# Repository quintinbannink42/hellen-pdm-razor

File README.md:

# PowerCore

Hellen-One **hardware** for **PowerCore**, a standalone automotive power distribution module (PDM) with a **Link Razor PDM**-compatible SuperSeal loom.

| | |
|---|---|
| **Product** | **PowerCore** (not an engine ECU) |
| **Connector** | 26-pin AMP SuperSeal 1.0 (Link “Connector C”) — pinout in [CONNECTOR.md](CONNECTOR.md) |
| **Main power** | M6 + / − (VBAT / GND), not on the SuperSeal |
| **MCU module** | [mega-mcu144](https://github.com/andreika-git/hellen-one/tree/master/modules/mega-mcu144) **rev ≥ 0.7** (STM32F767) |
| **I/O target** | 4× high-power (25 A / 80 A peak class) + 8× ADIO (8 A) |
| **KiCad stem** | `pdmrazora` (hellen-one: no dashes/underscores — **do not rename**) |
| **GitHub path** | `hellen-pdm-razor` (legacy repo name; product name is PowerCore) |
| **Default branch** | `main` (required by hellen-one automation) |

> **This is NOT [HELLCORE](https://github.com/quintinbannink42/HELLCORE).** HELLCORE is a separate project. PowerCore is a Hellen-One PDM carrier that matches the Link Razor loom connector.

Former working names (docs/history only): `hellen-pdm-razor`, Hellen Razor-class PDM.

## Docs

| File | Contents |
|------|----------|
| [POWERCORE_BRIEF.md](POWERCORE_BRIEF.md) | Product identity, tokens, Razor loom compatibility |
| [CONNECTOR.md](CONNECTOR.md) | Exact Razor-compatible 26-pin + M6 pinout (authoritative) |
| [PINMAP.md](PINMAP.md) | mega-mcu144 edge → HP / ADIO / system nets |
| [REV1_SPEC.md](REV1_SPEC.md) | Goals, architecture, e-fuse behaviour |
| [BLOCK_DIAGRAM.md](BLOCK_DIAGRAM.md) | Carrier block diagram |
| [BOARD.md](BOARD.md) | What’s stubbed vs next; module placement steps |
| [HARDWARE_BOM.md](HARDWARE_BOM.md) | Chosen PNs, kILIS, AmpsPerVolt TODOs |

## KiCad project

Open with **KiCad 8.x** (Hellen mega-mcu144 0.7 is K8). KiCad 9 also works. KiCad 6/7 will not open this module.

- `pdmrazora.kicad_pro` / `.kicad_sch` / `.kicad_pcb` (no dashes/underscores — hellen-one requirement)
- `revision.txt` → `BOARD_PREFIX=pdm` `BOARD_SUFFIX=razor` `BOARD_REVISION=a`

Schematic: SuperSeal **TE 6473418-1** vertical (Link Razor-compatible nets; same pin numbers as former RA 9-6437287-8), **split** M6 bolt-through bobbins (J2 VBAT+ north / J3 GND south, drivers between) + power entry/IGN_SW divider, sheets **MM144** / **HP** (**BTS50010-1TAD** ×4) / **ADIO** (**BTS7004-1EPP** ×8 + sense/PU). PCB: **109×98 mm** frame (was 104×93), mega-mcu144 0.7 west of a vertical SuperSeal EMI wall, power/PROFET east. J2 VBAT+ and J3 GND stay on opposite edges of the power field; HP×4 and ADIO×8 are mirrored about x=80. `PWR_OUT1–4` run on exposed F.Cu (F.Mask opened over the copper) with short B.Cu hops only at the module pad wall. DRC shorts/crossings/clearance are 0; the board is not fab-clean (see [BOARD.md](BOARD.md)). Parts/kILIS: [HARDWARE_BOM.md](HARDWARE_BOM.md).

## How to build (Hellen-One)

1. `git clone --recurse-submodules https://github.com/quintinbannink42/hellen-pdm-razor.git`
2. Open with **KiCad 8.x** (Hellen mega-mcu144 0.7 is K8). KiCad 9 also works. KiCad 6/7 will not open this module.
   Open `pdmrazora.kicad_pro`.
3. mega-mcu144 **0.7** is already on the frame (`M1000`). Refresh from `hellen-one/modules/mega-mcu144/0.7/` if the submodule moves.
4. Route SuperSeal / M6 / module pads per CONNECTOR.md / PINMAP.md; replace HP/ADIO schematic stubs with chosen PNs + sense parts.
5. Push to **`main`**. GitHub Action `.github/workflows/create-board.yaml` calls hellen-one create-board to merge module gerbers into `boards/`.
6. Daily workflows keep `hellen-one` and `kicad6-libraries` submodule refs updated.

Frame rules (from hellen-example FAQ):

- No `-` or `_` in KiCad filenames
- `aux_axis_origin` required; board origin at **bottom-left** (no negative coordinates)

## Firmware intent

Firmware is **not** this repo. See **[fw-powercore](https://github.com/quintinbannink42/fw-powercore)** (rusEFI custom board overlay: electronic fuse + channel map), based on [fw-custom-hellen144-f4](https://github.com/rusefi/fw-custom-hellen144-f4) / `hellen-common-mega144.mk`, with `protected_gpio` for HP1–4 + ADIO1–4 first. See PINMAP.md and REV1_SPEC.md.

## Submodules

```
hellen-one          https://github.com/andreika-git/hellen-one
kicad6-libraries    https://github.com/rusefi/kicad6-libraries
```

Skeleton mirrors [rusefi/hellen-example](https://github.com/rusefi/hellen-example).

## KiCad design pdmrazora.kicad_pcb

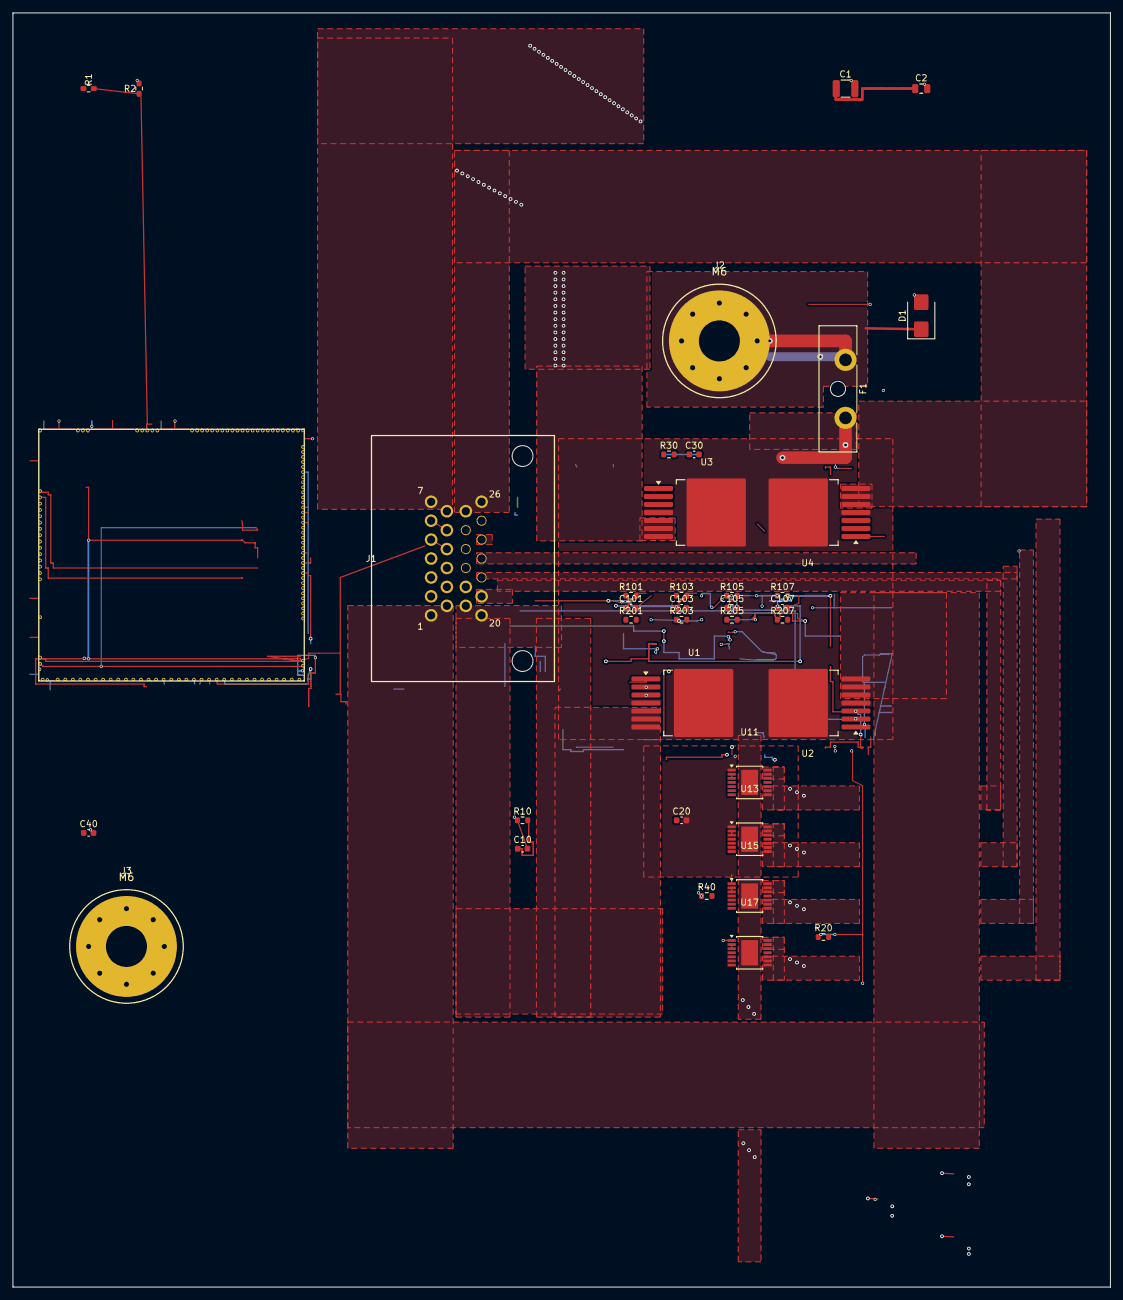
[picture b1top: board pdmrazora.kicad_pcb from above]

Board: 2 copper layers, 174.0 x 202.0 mm, 38 parts (0 on the bottom side), 32 nets.

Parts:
C1: 100u_50V; C_1210_3225Metric
C2: 100n; C_0805_2012Metric
C10, C20, C30, C40, C101, C103, C105, C107: 10n; C_0603_1608Metric
D1: SMBJ33CA; D_SMB
F1: 150A_MEGA_TBD; Fuseholder_Blade_ATO_Littelfuse_Pudenz_2_Pin
J1: 6473418-1; TE_6473418-1_SuperSeal26_Vertical
J2: M6_VBAT; M6_BoltThrough_Bobbin
J3: M6_GND; M6_BoltThrough_Bobbin
M1000: Module:mega-mcu144/0.7; mega-mcu144
R1: 100k; R_0603_1608Metric
R2: 10k; R_0603_1608Metric
R10, R20, R30, R40: 2k7; R_0603_1608Metric
R101, R103, R105, R107, R201, R203, R205, R207: 4k7; R_0603_1608Metric
U1, U2, U3, U4: BTS50010-1TAD; TO-263-7_TabPin4
U11, U13, U15, U17: BTS7004-1EPP; Infineon_PG-TSDSO-14-22

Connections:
ADIO1: J1.21, R201.2, U11.8, U11.9, U11.10, U11.12, U11.13, U11.14
ADIO3: J1.22, R203.2, U13.8, U13.9, U13.10, U13.12, U13.13, U13.14
ADIO5: J1.23, R205.2, U15.8, U15.9, U15.10, U15.12, U15.13, U15.14
ADIO7: J1.24, R207.2, U17.8, U17.9, U17.10, U17.12, U17.13, U17.14
CANH: J1.3, M1000.W12
CANL: J1.10, M1000.W13
GND: C1.2, C2.2, C10.2, C20.2, C30.2, C40.2, C101.2, C103.2, C105.2, C107.2, D1.2, J3.1, M1000.G, R2.2, R10.1, R20.1, R30.1, R40.1, R101.1, R103.1, R105.1, R107.1, U1.1, U2.1, U3.1, U4.1, U11.1, U13.1, U15.1, U17.1
IGN_SW: J1.4, R1.1
IN_AUX1: C10.1, M1000.S13, R10.2, U1.3
IN_AUX2: C20.1, M1000.S12, R20.2, U2.3
IN_AUX3: C30.1, M1000.S11, R30.2, U3.3
IN_AUX4: C40.1, M1000.S10, R40.2, U4.3
IN_MAP1: C101.1, M1000.S21, R101.2, U11.4
IN_MAP3: C103.1, M1000.S19, R103.2, U13.4
IN_O2S2: C105.1, M1000.S15, R105.2, U15.4
IN_RES2: C107.1, M1000.S14, R107.2, U17.4
IN_VIGN: M1000.N26, R1.2, R2.1
OUT_IO5: M1000.E7, U15.2, U15.3
OUT_IO7: M1000.E23, U17.2, U17.3
OUT_PWM1: M1000.E27, U1.2
OUT_PWM2: M1000.E17, U2.2
OUT_PWM3: M1000.E16, U3.2
OUT_PWM4: M1000.E15, U4.2
OUT_PWM5: M1000.E14, U11.2, U11.3
OUT_PWM7: M1000.E25, U13.2, U13.3
PWR_OUT1: J1.14, J1.20, U1.5, U1.6, U1.7
PWR_OUT2: J1.1, J1.8, U2.5, U2.6, U2.7
PWR_OUT3: J1.7, J1.13, U3.5, U3.6, U3.7
PWR_OUT4: J1.19, J1.26, U4.5, U4.6, U4.7
SENSOR_5V: J1.5, J1.11, M1000.E38, M1000.N30, M1000.W2, R201.1, R203.1, R205.1, R207.1
SENSOR_GND: J1.6, J1.12, M1000.E39, M1000.W1
VBAT: C1.1, C2.1, D1.1, F1.1, F1.2, J2.1, M1000.N27, U1.4, U2.4, U3.4, U4.4, U11.15, U13.15, U15.15, U17.15

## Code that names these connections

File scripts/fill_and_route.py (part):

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    r1b = pad_xy(get_pad(fps, "R1", "2"))
    r2a = pad_xy(get_pad(fps, "R2", "1"))
    r2b = pad_xy(get_pad(fps, "R2", "2"))
    add_track(board, jign[0], jign[1], jign[0], r1a[1], 0.4, "IGN_SW"); n += 1
    add_track(board, jign[0], r1a[1], r1a[0], r1a[1], 0.4, "IGN_SW"); n += 1
    add_track(board, r1b[0], r1b[1], r2a[0], r1b[1], 0.3, "IN_VIGN"); n += 1
    add_track(board, r2a[0], r1b[1], r2a[0], r2a[1], 0.3, "IN_VIGN"); n += 1
    add_track(board, r2b[0], r2b[1], r2b[0], r2b[1] + 2.0, 0.3, "GND"); n += 1
    add_via(board, r2b[0], r2b[1] + 2.0, "GND"); n += 1
    # IN_VIGN to N26 via B.Cu north edge
    mx, my = pad_xy(get_pad(fps, "M1000", "N26"))
    add_track(board, r1b[0], r1b[1], r1b[0] - 2.5, r1b[1], 0.3, "IN_VIGN"); n += 1
    add_via(board, r1b[0] - 2.5, r1b[1], "IN_VIGN"); n += 1
    add_track(board, r1b[0] - 2.5, r1b[1], r1b[0] - 2.5, 10.0, 0.3, "IN_VIGN", B_Cu); n += 1
    add_track(board, r1b[0] - 2.5, 10.0, mx, 10.0, 0.3, "IN_VIGN", B_Cu); n += 1
    add_via(board, mx, 10.0, "IN_VIGN"); n += 1
    add_track(board, mx, 10.0, mx, my, 0.3, "IN_VIGN"); n += 1

    # CAN — left edge B.Cu, exclusive x=4.5 / 5.5
    for net, mpad, jpin, lane_x in [("CANH", "W12", "3", 4.0), ("CANL", "W13", "10", 7.0)]:
        mx, my = pad_xy(get_pad(fps, "M1000", mpad))
        jx, jy = pad_xy(get_pad(fps, "J1", jpin))
        add_track(board, mx, my, lane_x, my, 0.3, net); n += 1
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    # SENSOR_5V: B.Cu bus along top (y=5), clear of ADIO B corridors
    bus_y = 5.0
    e38 = pad_xy(get_pad(fps, "M1000", "E38"))
    add_track(board, e38[0], e38[1], 52.5, e38[1], 0.4, "SENSOR_5V"); n += 1
    add_via(board, 52.5, e38[1], "SENSOR_5V"); n += 1
    add_track(board, 52.5, e38[1], 52.5, bus_y, 0.4, "SENSOR_5V", B_Cu); n += 1
    add_track(board, 52.5, bus_y, 132.0, bus_y, 0.5, "SENSOR_5V", B_Cu); n += 1
    for r in range(201, 209):
        rx, ry = pad_xy(get_pad(fps, f"R{r}", "1"))
        side = rx - 1.8  # west of PU, away from ADIO OUT east pads
        add_track(board, rx, ry, side, ry, 0.3, "SENSOR_5V"); n += 1
        add_via(board, side, ry, "SENSOR_5V"); n += 1
        add_track(board, side, ry, side, bus_y, 0.3, "SENSOR_5V", B_Cu); n += 1
        # tee into bus
        add_track(board, side, bus_y, side + 0.01, bus_y, 0.3, "SENSOR_5V", B_Cu); n += 1
    for jp in ("5", "11"):
        jx, jy = pad_xy(get_pad(fps, "J1", jp))
        ex = 81.0 + (0.8 if jp == "5" else 0.0)
        add_track(board, jx, jy, ex, jy, 0.4, "SENSOR_5V"); n += 1
        add_via(board, ex, jy, "SENSOR_5V"); n += 1
        add_track(board, ex, jy, ex, bus_y, 0.4, "SENSOR_5V", B_Cu); n += 1
    n30 = pad_xy(get_pad(fps, "M1000", "N30"))
    w2 = pad_xy(get_pad(fps, "M1000", "W2"))
    add_track(board, n30[0], n30[1], n30[0], 10.0, 0.35, "SENSOR_5V"); n += 1
    add_via(board, n30[0], 10.0, "SENSOR_5V"); n += 1
    add_track(board, n30[0], 10.0, n30[0], bus_y, 0.35, "SENSOR_5V", B_Cu); n += 1
    add_track(board, n30[0], bus_y, 52.5, bus_y, 0.35, "SENSOR_5V", B_Cu); n += 1
    add_track(board, w2[0], w2[1], 5.0, w2[1], 0.35, "SENSOR_5V"); n += 1
    add_via(board, 5.0, w2[1], "SENSOR_5V"); n += 1
    add_track(board, 5.0, w2[1], 5.0, bus_y, 0.35, "SENSOR_5V", B_Cu); n += 1
    add_track(board, 5.0, bus_y, 52.5, bus_y, 0.35, "SENSOR_5V", B_Cu); n += 1

    # SENSOR_GND dedicated
    a = pad_xy(get_pad(fps, "J1", "6"))
    b = pad_xy(get_pad(fps, "J1", "12"))
    add_track(board, a[0], a[1], b[0], a[1], 0.4, "SENSOR_GND"); n += 1
    add_track(board, b[0], a[1], b[0], b[1], 0.4, "SENSOR_GND"); n += 1
    e39 = pad_xy(get_pad(fps, "M1000", "E39"))
    add_track(board, e39[0], e39[1], 52.5, e39[1], 0.4, "SENSOR_GND"); n += 1
    add_via(board, 52.5, e39[1], "SENSOR_GND"); n += 1
    # B highway at y=60 (below SENSOR_5V bus)
    sg_y = 70.0
    add_track(board, 52.5, e39[1], 52.5, sg_y, 0.4, "SENSOR_GND", B_Cu); n += 1
    add_track(board, 52.5, sg_y, a[0] + 2.0, sg_y, 0.4, "SENSOR_GND", B_Cu); n += 1
    add_via(board, a[0] + 2.0, sg_y, "SENSOR_GND"); n += 1
    add_track(board, a[0] + 2.0, sg_y, a[0] + 2.0, a[1], 0.4, "SENSOR_GND"); n += 1
    add_track(board, a[0] + 2.0, a[1], a[0], a[1], 0.4, "SENSOR_GND"); n += 1
    w1 = pad_xy(get_pad(fps, "M1000", "W1"))
    add_track(board, w1[0], w1[1], 2.5, w1[1], 0.35, "SENSOR_GND"); n += 1
    add_via(board, 2.5, w1[1], "SENSOR_GND"); n += 1
    add_track(board, 2.5, w1[1], 2.5, sg_y, 0.35, "SENSOR_GND", B_Cu); n += 1
    add_track(board, 2.5, sg_y, 52.5, sg_y, 0.35, "SENSOR_GND", B_Cu); n += 1
    return n


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    r1b = pad_xy(get_pad(fps, "R1", "2"))
    r2a = pad_xy(get_pad(fps, "R2", "1"))
    mx, my = pad_xy(get_pad(fps, "M1000", "N26"))
    add_track(board, jign[0], jign[1], jign[0], r1a[1], 0.4, "IGN_SW"); n += 1
    add_track(board, jign[0], r1a[1], r1a[0], r1a[1], 0.4, "IGN_SW"); n += 1
    add_track(board, r1b[0], r1b[1], r2a[0], r1b[1], 0.3, "IN_VIGN"); n += 1
    add_track(board, r2a[0], r1b[1], r2a[0], pad_xy(get_pad(fps, "R2", "1"))[1], 0.3, "IN_VIGN"); n += 1
    add_track(board, r1b[0], r1b[1], 58.0, r1b[1], 0.3, "IN_VIGN"); n += 1
    add_via(board, 58.0, r1b[1], "IN_VIGN"); n += 1
    add_track(board, 58.0, r1b[1], 58.0, 6.5, 0.3, "IN_VIGN", B_Cu); n += 1
    add_track(board, 58.0, 6.5, mx, 6.5, 0.3, "IN_VIGN", B_Cu); n += 1
    add_via(board, mx, 6.5, "IN_VIGN"); n += 1
    add_track(board, mx, 6.5, mx, my, 0.3, "IN_VIGN"); n += 1
    return n


def route_can_only(board, fps):
    n = 0
    for net, mpad, jpin, lane_x in [("CANH", "W12", "3", 4.0), ("CANL", "W13", "10", 7.0)]:
        mx, my = pad_xy(get_pad(fps, "M1000", mpad))
        jx, jy = pad_xy(get_pad(fps, "J1", jpin))
        add_track(board, mx, my, lane_x, my, 0.3, net); n += 1
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def route_sensor_only(board, fps):
    n = 0
    e38 = pad_xy(get_pad(fps, "M1000", "E38"))
    add_track(board, e38[0], e38[1], 52.0, e38[1], 0.4, "SENSOR_5V"); n += 1
    add_via(board, 52.0, e38[1], "SENSOR_5V"); n += 1
    add_track(board, 52.0, e38[1], 52.0, 128.0, 0.4, "SENSOR_5V", B_Cu); n += 1
    add_track(board, 52.0, 128.0, 140.0, 128.0, 0.4, "SENSOR_5V", B_Cu); n += 1
    for i, jp in enumerate(("5", "11")):
        jx, jy = pad_xy(get_pad(fps, "J1", jp))
        ex = 138.0 - i * 1.5
        add_via(board, ex, 128.0, "SENSOR_5V"); n += 1
        add_track(board, ex, 128.0, ex, jy, 0.4, "SENSOR_5V"); n += 1
        add_track(board, ex, jy, jx, jy, 0.4, "SENSOR_5V"); n += 1
    a5 = pad_xy(get_pad(fps, "J1", "5"))
    a11 = pad_xy(get_pad(fps, "J1", "11"))
    add_track(board, a5[0], a5[1], a11[0], a5[1], 0.4, "SENSOR_5V"); n += 1
    add_track(board, a11[0], a5[1], a11[0], a11[1], 0.4, "SENSOR_5V"); n += 1
    n30 = pad_xy(get_pad(fps, "M1000", "N30"))
    add_track(board, n30[0], n30[1], n30[0], 8.0, 0.35, "SENSOR_5V"); n += 1
    add_via(board, n30[0], 8.0, "SENSOR_5V"); n += 1
    add_track(board, n30[0], 8.0, 52.0, 8.0, 0.35, "SENSOR_5V", B_Cu); n += 1
    add_track(board, 52.0, 8.0, 52.0, e38[1], 0.35, "SENSOR_5V", B_Cu); n += 1
    w2 = pad_xy(get_pad(fps, "M1000", "W2"))
    add_track(board, w2[0], w2[1], 5.0, w2[1], 0.35, "SENSOR_5V"); n += 1
    add_via(board, 5.0, w2[1], "SENSOR_5V"); n += 1
    add_track(board, 5.0, w2[1], 5.0, 128.0, 0.35, "SENSOR_5V", B_Cu); n += 1
    add_track(board, 5.0, 128.0, 52.0, 128.0, 0.35, "SENSOR_5V", B_Cu); n += 1
    a = pad_xy(get_pad(fps, "J1", "6"))
    b = pad_xy(get_pad(fps, "J1", "12"))
    add_track(board, a[0], a[1], b[0], a[1], 0.4, "SENSOR_GND"); n += 1
    add_track(board, b[0], a[1], b[0], b[1], 0.4, "SENSOR_GND"); n += 1
    sg = 129.0
    add_track(board, a[0], a[1], a[0], sg, 0.4, "SENSOR_GND"); n += 1
    add_via(board, a[0], sg, "SENSOR_GND"); n += 1
    e39 = pad_xy(get_pad(fps, "M1000", "E39"))
    add_track(board, e39[0], e39[1], 52.0, e39[1], 0.4, "SENSOR_GND"); n += 1
    add_via(board, 52.0, e39[1], "SENSOR_GND"); n += 1
    add_track(board, 52.0, e39[1], 52.0, sg, 0.4, "SENSOR_GND", B_Cu); n += 1
    add_track(board, 52.0, sg, a[0], sg, 0.4, "SENSOR_GND", B_Cu); n += 1
    w1 = pad_xy(get_pad(fps, "M1000", "W1"))
    add_track(board, w1[0], w1[1], 2.5, w1[1], 0.35, "SENSOR_GND"); n += 1
    add_via(board, 2.5, w1[1], "SENSOR_GND"); n += 1
    add_track(board, 2.5, w1[1], 2.5, sg, 0.35, "SENSOR_GND", B_Cu); n += 1
    add_track(board, 2.5, sg, 52.0, sg, 0.35, "SENSOR_GND", B_Cu); n += 1
    return n


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
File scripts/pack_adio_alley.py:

#!/usr/bin/env python3
"""Open an IS alley by spreading ADIO columns 0.35 mm per gap.

Column 0 stays. Columns 1..3 move east 0.35 / 0.70 / 1.05 mm, and copper that
already sits inside that column (both ends, or a vertical fanout jogged at the
top of the package) moves with it. The IN_AUX1 spine at x=72 and the IN_AUX2/4
spines at x=80 / 80.8 / 81.6 are shifted on their own so the new pads do not
land on them.

Does not move J1, M1000, J2, or J3. Does not bridge F1. Does not add a
SENSOR_GND pour. Does not replay the long-haul routers.
"""
from __future__ import annotations

import shutil
import sys
from pathlib import Path

import pcbnew
from pcbnew import PCB_TRACK, ToMM

sys.path.insert(0, str(Path(__file__).resolve().parent))
import close_carrier_rats as cr  # noqa: E402

# Local copper only. The x=72 and x=80 spines are outside these bands.
LOCAL = (
    (55.80, 64.20, 0.35),
    (64.20, 72.35, 0.70),
    (72.35, 79.75, 1.05),
)
Y_LO = 67.05
Y_HI = 91.80
# Alternating jog heights just above the C30/R30 pads and below the driver pads.
JOG_Y = (66.52, 66.98)

COLUMNS = {
    0.00: ["U11", "U15", "R201", "R205", "R101", "R105", "C101", "C105"],
    0.35: ["U12", "U16", "R202", "R206", "R102", "R106", "C102", "C106"],
    0.70: ["U13", "U17", "R203", "R207", "R103", "R107", "C103", "C107"],
    1.05: ["U14", "U18", "R204", "R208", "R104", "R108", "C104", "C108"],
}

# East-spine endpoints that must clear U14's new pad edge (x = 80.555).
SPINE_NETS = {"IN_AUX2", "IN_AUX4"}
SPINE_DX = (
    (80.00, 1.00),
    (80.80, 1.00),
    (81.60, 1.00),
)


def mm_of(p) -> tuple[float, float]:
    return ToMM(p.x), ToMM(p.y)


def local_dx(x: float, y: float) -> float:
    if y < Y_LO or y > Y_HI:
        return 0.0
    for a, b, dx in LOCAL:
        if a <= x < b:
            return dx
    return 0.0


def set_ends(track, x1, y1, x2, y2) -> None:
    track.SetStart(cr.mm(x1, y1))
    track.SetEnd(cr.mm(x2, y2))


def add_seg(board, x1, y1, x2, y2, width, net, layer) -> None:
    if abs(x1 - x2) < 0.001 and abs(y1 - y2) < 0.001:
        return
    tr = PCB_TRACK(board)
    tr.SetStart(cr.mm(x1, y1))
    tr.SetEnd(cr.mm(x2, y2))
    tr.SetWidth(cr.mm(width))
    tr.SetLayer(layer)
    tr.SetNet(net)
    board.Add(tr)


def spine_dx(net: str, x: float, y: float) -> float:
    if net not in SPINE_NETS or y < 63.50:
        return 0.0
    for origin, dx in SPINE_DX:
        if abs(x - origin) < 0.06:
            return dx
    return 0.0


def shift_east_spines(board) -> int:
    n = 0
    for t in list(board.GetTracks()):
        if cr.is_via(t):
            continue
        net = t.GetNetname() or ""
        x1, y1 = mm_of(t.GetStart())
        x2, y2 = mm_of(t.GetEnd())
        d1 = spine_dx(net, x1, y1)
        d2 = spine_dx(net, x2, y2)
        if abs(d1) < 1e-9 and abs(d2) < 1e-9:
            continue
        set_ends(t, x1 + d1, y1, x2 + d2, y2)
        n += 1
    return n


def extend_in_aux1(board) -> None:
    """The x=72 bus stays put except the end that meets the jogged spine."""
    for t in list(board.GetTracks()):
        if cr.is_via(t) or (t.GetNetname() or "") != "IN_AUX1":
            continue
        x1, y1 = mm_of(t.GetStart())
        x2, y2 = mm_of(t.GetEnd())
        if abs(y1 - 72.0) < 0.06 and abs(x1 - 72.0) < 0.06 and abs(x2 - 72.0) > 0.5:
            set_ends(t, 72.70, y1, x2, y2)
            print("  extend IN_AUX1 bus to x=72.70")
        elif abs(y2 - 72.0) < 0.06 and abs(x2 - 72.0) < 0.06 and abs(x1 - 72.0) > 0.5:
            set_ends(t, x1, y1, 72.70, y2)
            print("  extend IN_AUX1 bus to x=72.70")


def move_local_copper(board) -> tuple[int, int]:
    moved = 0
    splits = []
    for t in list(board.GetTracks()):
        if cr.is_via(t):
            x, y = mm_of(t.GetPosition())
            dx = local_dx(x, y)
            if abs(dx) > 1e-9:
                t.SetPosition(cr.mm(x + dx, y))
                moved += 1
            continue
        x1, y1 = mm_of(t.GetStart())
        x2, y2 = mm_of(t.GetEnd())
        d1 = local_dx(x1, y1)
        d2 = local_dx(x2, y2)
        if abs(d1) < 1e-9 and abs(d2) < 1e-9:
            continue
        vertical = abs(x1 - x2) < 0.20
        one_sided = (abs(d1) < 1e-9) ^ (abs(d2) < 1e-9)
        if vertical and one_sided:
            splits.append(t)
            continue
        # Ends in different columns stay horizontal: each end follows its own
        # column, so the segment lengthens instead of rotating onto a neighbor.
        set_ends(t, x1 + d1, y1, x2 + d2, y2)
        moved += 1
    splits.sort(key=lambda t: mm_of(t.GetStart())[0])
    for i, t in enumerate(splits):
        x1, y1 = mm_of(t.GetStart())
        x2, y2 = mm_of(t.GetEnd())
        if local_dx(x1, y1) > 0:
            x, y_in, y_out, dx = x1, y1, y2, local_dx(x1, y1)
        else:
            x, y_in, y_out, dx = x2, y2, y1, local_dx(x2, y2)
        jog_y = JOG_Y[i % 2]
        # Keep the jog on the outside of the package, between the two ends.
        if not (min(y_in, y_out) + 0.05 < jog_y < max(y_in, y_out) - 0.05):
            jog_y = (min(y_in, y_out) + Y_LO) / 2
        width = ToMM(t.GetWidth())
        net = t.GetNet()
        layer = t.GetLayer()
        set_ends(t, x, y_out, x, jog_y)
        add_seg(board, x, jog_y, x + dx, jog_y, width, net, layer)
        add_seg(board, x + dx, jog_y, x + dx, y_in, width, net, layer)
        moved += 1
    return moved, len(splits)


def move_footprints(board) -> list[tuple[str, float, float, float, float]]:
    moves = []
    for dx, refs in COLUMNS.items():
        delta = cr.mm(dx, 0.0)
        for ref in refs:
            fp = board.FindFootprintByReference(ref)
            x0, y0 = mm_of(fp.GetPosition())
            if abs(dx) > 1e-9:
                fp.Move(delta)
            x1, y1 = mm_of(fp.GetPosition())
            moves.append((ref, x0, y0, x1, y1))
    return moves


def apply(board) -> list[tuple[str, float, float, float, float]]:
    n, nsplit = move_local_copper(board)
    print(f"local copper {n}, fanout splits {nsplit}")
    print(f"east spines shifted: {shift_east_spines(board)}")
    extend_in_aux1(board)
    return move_footprints(board)


def main() -> int:
    src = Path(sys.argv[1]) if len(sys.argv) > 1 else cr.PCB
    dst = Path(sys.argv[2]) if len(sys.argv) > 2 else src
    if src.resolve() != dst.resolve():
        shutil.copy(src, dst)
    board = pcbnew.LoadBoard(str(dst))
    moves = apply(board)
    for ref, x0, y0, x1, y1 in moves:
        if abs(x1 - x0) > 1e-6:
            print(f"  {ref:6} ({x0:.3f},{y0:.3f}) -> ({x1:.3f},{y1:.3f})")
    if cr.fuse_bridged(board):
        raise SystemExit("fuse bridged during pack")
    if cr.sensor_pours(board):
        raise SystemExit("SENSOR_GND pour appeared")
    cr.fill_zones(board)
    board.Save(str(dst))
    cr.downgrade_to_k8(dst)
    print(f"wrote {dst}")
    return 0


if __name__ == "__main__":
    raise SystemExit(main())
